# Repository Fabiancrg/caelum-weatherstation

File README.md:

| Supported Targets | ESP32-C6 | ESP32-H2 |
| ----------------- |  -------- | -------- |

# Caelum - Zigbee Weather Station

## Project Description

This project implements a battery-powered environmental monitoring device using ESP32-C6/H2 with Zigbee connectivity. The device features a 3-endpoint design with remote sleep configuration, optimized for low-power operation with deep sleep support and extended wake time during network join.

This project is based on the examples provided in the ESP Zigbee SDK:

* [ESP Zigbee SDK Docs](https://docs.espressif.com/projects/esp-zigbee-sdk)
* [ESP Zigbee SDK Repo](https://github.com/espressif/esp-zigbee-sdk)

## Device Features

### 🌐 Zigbee Endpoints Overview

| Endpoint | Device Type | Clusters | Description |
|----------|-------------|----------|-------------|
| **1** | Environmental Sensor | Temperature, Humidity, Pressure, Battery, OTA | BME280 sensor via I2C |
| **2** | Rain Gauge | Analog Input | Tipping bucket rain sensor with rainfall totals |
| **3** | Sleep Configuration | Analog Input | Remote sleep duration control (60-7200 seconds) |
| **4** | LED Debug Control | On/Off | WS2812 RGB LED status indicator (remote control) |

### 💡 LED Debug Feature (Optional)

The device includes an optional WS2812 RGB LED on GPIO8 (ESP32-H2 SuperMini) that provides visual feedback:
- **Blue (Steady)**: Connected to Zigbee network
- **Orange (Blinking)**: Joining/searching for network  
- **White (Brief Flash)**: Rain pulse detected
- **Off**: Deep sleep or disabled via Zigbee

This feature can be controlled remotely via Zigbee2MQTT (endpoint 4) and disabled to conserve battery. See [LED_DEBUG_FEATURE.md](LED_DEBUG_FEATURE.md) for complete documentation.

### 📋 Detailed Endpoint Descriptions

#### **Endpoint 1: Environmental Monitoring & Power Management**
- **Hardware**: BME280 sensor via I2C
  - **ESP32-H2**: SDA: GPIO10, SCL: GPIO11
  - **ESP32-C6**: SDA: GPIO6, SCL: GPIO7
- **Measurements**: 
  - 🌡️ **Temperature**: -40°C to +85°C (±1°C accuracy)
  - 💧 **Humidity**: 0-100% RH (±3% accuracy) 
  - 🌪️ **Pressure**: 300-1100 hPa (±1 hPa accuracy)
  - 🔋 **Battery Monitoring**: Li-Ion voltage (2.7V-4.2V) and percentage
- **Battery Monitoring**:
  - **Hardware**: GPIO4 (ADC1_CH4) with voltage divider (2x 100kΩ resistors)
  - **Voltage**: Real-time battery voltage in 0.1V units
  - **Percentage**: Battery level 0-100% based on Li-Ion discharge curve
  - **Calibration**: ESP32-H2 ADC correction factor (1.604x) for accurate readings
  - **Power Configuration Cluster**: Standard Zigbee battery attributes
  - **Optimized Reading**: 
    - Time-based hourly intervals (3600 seconds) with NVS persistence
    - 3 ADC samples (reduced from 10) for ~70% ADC power savings
    - No delays between samples for ~90% overhead reduction
    - Total battery monitoring power: ~12µAh/day (98% reduction from ~480µAh/day)
    - Always reports on first boot/pairing, then hourly regardless of wake frequency
- **Features**: Automatic reporting during wake cycles, Zigbee-standard units
- **Use Case**: Weather monitoring, HVAC automation, air quality tracking, battery-powered applications

#### **Endpoint 2: Rain Gauge System**
- **Hardware**: Tipping bucket rain gauge with reed switch
  - **ESP32-H2**: GPIO12 (RTC-capable for sleep wake-up)
  - **ESP32-C6**: GPIO5 (RTC-capable for sleep wake-up)
- **Measurements**: Cumulative rainfall in millimeters (0.36mm per tip)
- **Features**: 
  - Advanced debouncing (200ms + 1000ms bounce settle)
  - Persistent storage (NVS) for total tracking
  - Smart reporting (1mm threshold OR hourly)
  - Network-aware operation (only active when connected)
  - **Both targets**: Wake from deep sleep on rain detection
  - **Time-based hourly reading**: Uses NVS persistence to ensure true 1-hour intervals regardless of wake frequency
- **Specifications**: 
  - Maximum rate: 200mm/hour supported
  - Accuracy: ±0.36mm per bucket tip
  - Storage: Non-volatile total persistence across reboots
  - Rain-proof interval tracking: Hourly battery reading even during frequent rain events
- **Use Case**: Weather station, irrigation control, flood monitoring

#### **Endpoint 3: Sleep Configuration**
- **Hardware**: Software-only (virtual endpoint)
- **Control**: Sleep duration in seconds (60-7200s range)
- **Features**:
  - Remote configuration via Zigbee2MQTT or Home Assistant
  - Persistent storage (NVS) - survives reboots
  - Real-time updates - changes apply on next wake cycle
  - Default: 900 seconds (15 minutes)
- **Use Case**: 
  - Battery optimization (longer intervals = longer battery life)
  - Seasonal adjustments (frequent updates in rainy season)
  - Dynamic power management based on weather conditions

#### **Endpoint 4: LED Debug Control**
- **Hardware**: WS2812 RGB LED (ESP32-H2 SuperMini)
  - **GPIO**: GPIO8
  - **Driver**: espressif/led_strip ~2.0.0
- **LED States**:
  - 🔵 **Blue (Steady)**: Connected to Zigbee network
  - 🟠 **Orange (Blinking)**: Searching/joining network
  - ⚪ **White (Flash)**: Rain pulse detected (100ms)
  - ⚫ **Off**: Deep sleep or disabled
- **Control**: On/Off cluster for remote enable/disable
- **Features**:
  - Remote control via Zigbee2MQTT switch
  - Default state: Enabled (ON)
  - Minimal battery impact (~20mA when active, off during sleep)
  - Visual feedback for debugging and network status
- **Use Case**: 
  - Development and testing (visual network status)
  - Field deployment debugging
  - Can be disabled remotely to conserve battery
- **Documentation**: See [LED_DEBUG_FEATURE.md](LED_DEBUG_FEATURE.md) for details

### 🔧 Hardware Configuration

#### **Required Components**
- ESP32-C6 or ESP32-H2 development board
- BME280 environmental sensor module
- Tipping bucket rain gauge with reed switch
- Li-Ion battery (with protection circuit, 5V output recommended)
- Voltage divider (2x 100kΩ resistors for battery monitoring)
- Zigbee coordinator (ESP32-H2 or commercial gateway)

#### **Pin Assignments**

**ESP32-H2 (Recommended)**
```
GPIO 4  - Battery voltage input (ADC1_CH4 with voltage divider)
GPIO 8  - WS2812 RGB LED (debug indicator, optional)
GPIO 9  - Built-in button (factory reset)
GPIO 10 - I2C SDA (BME280)
GPIO 11 - I2C SCL (BME280) 
GPIO 12 - Rain gauge input (RTC-capable)*
```

**ESP32-C6**
```
GPIO 4  - Battery voltage input (ADC1_CH4 with voltage divider)
GPIO 5  - Rain gauge input (RTC-capable)*
GPIO 6  - I2C SDA (BME280)
GPIO 7  - I2C SCL (BME280) 
GPIO 9  - Built-in button (factory reset)
```

*Both targets now use RTC-capable GPIO pins for rain detection during deep sleep

**Battery Voltage Divider Circuit**
```
Battery+ ──┬── 100kΩ ──┬── 100kΩ ── GND
           │           │
           │           └── GPIO4 (ADC input)
           │
           └── 5V output (to ESP32 power)
```
Note: Voltage divider monitors the cell voltage (2.7V-4.2V) while the battery pack provides 5V regulated output

### � Zigbee Integration
- **Protocol**: Zigbee 3.0  
- **Device Type**: End Device (sleepy end device for battery operation)
- **Supported Channels**: 11-26 (2.4 GHz)
- **Compatible**: Zigbee2MQTT, Home Assistant ZHA, Hubitat
- **OTA Support**: Over-the-air firmware updates enabled (see [OTA_GUIDE.md](OTA_GUIDE.md))

### ⚡ Power Management
- **Deep Sleep Mode**: Configurable intervals (60-7200 seconds, default 15 minutes)
  - **Configurable via Zigbee2MQTT**: Adjust sleep duration remotely from Home Assistant
  - **Connected**: Uses configured interval (default 15 minutes)
  - **Disconnected**: 30-second intervals for quick reconnection
  - **Max retries**: After 20 attempts (10 minutes), reduces to half configured duration
  - **Extended wake time**: Device stays awake for 60 seconds when not connected (instead of 10s) to allow Zigbee join process to complete
- **Wake-up Sources**:
  - Timer (configurable 60-7200 seconds)
  - **Rain detection during deep sleep** (both targets support RTC wake-up)
    - **ESP32-H2**: GPIO12 (RTC-capable)
    - **ESP32-C6**: GPIO5 (RTC-capable)
- **Network Retry Logic**: 
  - Prevents deep sleep when not connected to ensure reliable pairing
  - Extended 60-second wake period for join process completion
  - Connection success triggers 15-second reporting window before sleep
- **Battery Life**: Optimized for extended operation on battery power
  - **Total Power Consumption**: ~230µAh/day (optimized from ~700µAh/day)
  - **Battery monitoring**: ~12µAh/day (hourly readings with time-based intervals)
  - **Deep sleep**: 7-10µA baseline
  - **Active time**: ~100mA during 15-minute wake cycles
- **Battery Estimate**: 
  - **2500mAh battery**: ~10.9 years (optimized from ~3.5 years)
  - **Optimization breakdown**: 
    - 3 ADC samples instead of 10 (70% ADC power savings)
    - No delays between samples (90% overhead reduction)
    - Time-based hourly intervals (vs. every wake cycle)
    - Total battery monitoring: 98% power reduction

## 🚀 Quick Start

### Prerequisites

```bash
# Install ESP-IDF v5.5.1 or later
git clone -b v5.5.1 --recursive https://github.com/espressif/esp-idf.git
cd esp-idf
# For ESP32-H2 (recommended)
./install.sh esp32h2
# For ESP32-C6
./install.sh esp32c6
. ./export.sh
```

### Configure the Project
```bash
# For ESP32-H2 (recommended for better power management)
idf.py set-target esp32h2
# For ESP32-C6  
idf.py set-target esp32c6
idf.py menuconfig
```

### Build and Flash
```bash
# Erase previous data (recommended for first flash)
idf.py -p [PORT] erase-flash

# Build and flash the project
idf.py -p [PORT] flash monitor
```

### 🛠️ Configuration

### Device Operation

#### **Factory Reset**
- **Built-in Button (GPIO 9)**:
  - Long press (5s): Factory reset device

#### **Automatic Features**
- Environmental data reported during wake cycles
- Rain gauge totals stored persistently in NVS
- Smart rainfall reporting (1mm increments or hourly)
- Network connection status monitoring
- Deep sleep after data reporting (15-second window when connected, 60 seconds when not connected)
- Sleep duration remotely configurable via Zigbee2MQTT (60-7200 seconds)

### 📡 Data Reporting
- **Temperature/Humidity/Pressure**: Reported during wake cycles
- **Rainfall**: Immediate on tip detection (>1mm) or hourly
- **Sleep Duration**: Configurable 60-7200 seconds (default 15 minutes)
- **Sleep Cycle**: Configurable via Endpoint 3 for battery optimization

## 📊 Example Output

### Device Initialization
```
I (403) app_start: Starting scheduler on CPU0
I (408) WEATHER_STATION: Initialize Zigbee stack
I (558) WEATHER_STATION: Deferred driver initialization successful
I (568) WEATHER_STATION: BME280 sensor initialized successfully
I (578) WEATHER_STATION: Rain gauge initialized. Current total: 0.00 mm
I (578) WEATHER_STATION: Start network steering
```

### Network Connection
```
I (3558) WEATHER_STATION: Joined network successfully (Extended PAN ID: 74:4d:bd:ff:fe:63:f7:30, PAN ID: 0x13af, Channel:13, Short Address: 0x7c16)
I (3568) RAIN_GAUGE: Rain gauge enabled - device connected to Zigbee network
```

### Sensor Data Reporting
```
I (8000) WEATHER_STATION: 🌡️ Temperature: 22.35°C reported to Zigbee  
I (8010) WEATHER_STATION: 💧 Humidity: 45.20% reported to Zigbee
I (8020) WEATHER_STATION: 🌪️ Pressure: 1013.25 hPa reported to Zigbee
I (8030) BATTERY: 🔋 Li-Ion Battery: 4.17V (98%) - Zigbee values: 41 (0.1V), 196 (%*2)
I (8040) WEATHER_STATION: 📡 Temp: 22.4°C
I (8050) WEATHER_STATION: 📡 Humidity: 45.2%
I (8060) WEATHER_STATION: 📡 Pressure: 1013.3 hPa
```

### Rain Gauge Activity
```  
I (10000) RAIN_GAUGE: 🔍 Rain gauge interrupt received on GPIO18 (enabled: YES)
I (10010) RAIN_GAUGE: 🌧️ Rain pulse #1 detected! Total: 0.36 mm (+0.36 mm)
I (10020) RAIN_GAUGE: ✅ Rainfall total 0.36 mm reported to Zigbee
I (10030) WEATHER_STATION: 📡 Rain: 0.36 mm
```

### Deep Sleep Entry
```
I (18000) WEATHER_STATION: ⏳ Preparing for deep sleep...
I (18010) WEATHER_STATION: 💤 Entering deep sleep for 900 seconds (15 minutes)
```

## 🏠 Home Assistant Integration

When connected to Zigbee2MQTT or other Zigbee coordinators, the device appears as:

- **4x Sensor entities**: Temperature, Humidity, Pressure, Battery Percentage
- **1x Sensor entity**: Battery Voltage (mV)
- **1x Sensor entity**: Rainfall total with automatic updates
- **1x Number entity**: Sleep duration control (60-7200 seconds)
- **1x Switch entity**: LED debug control (enable/disable status indicator)

### Zigbee2MQTT Integration

A custom external converter is provided for full feature support with Zigbee2MQTT. See [ZIGBEE2MQTT_CONVERTER.md](ZIGBEE2MQTT_CONVERTER.md) for:
- Converter installation instructions
- Multi-endpoint support configuration
- Sleep duration control setup
- Home Assistant automation examples

### Device Information
- **Manufacturer**: ESPRESSIF
- **Model**: caelum
- **Firmware Version**: Managed via CMakeLists.txt (PROJECT_VER, BUILD_NUMBER)
  - Generated header approach using `version.h.in` template
  - Single source of truth for all version macros
  - Automatically propagated to Zigbee Basic cluster attributes
- **Supported**: Zigbee2MQTT with custom external converter (`caelum-weather-station.js`)

## 🔧 Configuration

### Version Management

Version information is centrally managed in `CMakeLists.txt`:

```cmake
set(PROJECT_VER "1.0")           # Major.Minor version
set(BUILD_NUMBER 0)              # Build/patch number
```

The build system automatically:
- Generates `build/generated/version.h` from `version.h.in` template
- Populates all version macros (FW_VERSION, FW_DATE_CODE, OTA_FILE_VERSION, etc.)
- Propagates to Zigbee Basic cluster (swBuildId, dateCode, applicationVersion)
- Updates OTA cluster attributes for firmware update tracking

### Application Configuration

Key parameters can be adjusted in `main/esp_zb_weather.h`:
- Default sleep duration: 900 seconds (15 minutes) - can be changed via Endpoint 3
- Sleep duration range: 60-7200 seconds (1 minute to 2 hours)
- Network retry interval: 30 seconds when disconnected
- Maximum connection retries: 20 attempts before reducing sleep interval
- Rain tip bucket volume: 0.36mm per tip
- Extended wake time: 60 seconds when not connected (for join process)
- **Battery monitoring interval**: 3600 seconds (1 hour) - time-based with NVS persistence
- **Battery ADC samples**: 3 samples averaged (optimized from 10)
- **Battery monitoring power**: ~12µAh/day (98% reduction from original ~480µAh/day)
- **LED Debug**: Optional WS2812 RGB LED on GPIO8 (ESP32-H2), controllable via Zigbee

## 📝 Project Structure

```
WeatherStation/
├── main/
│   ├── esp_zb_weather.c     # Main Zigbee stack, 4-endpoint logic, network retry, LED control
│   ├── esp_zb_weather.h     # Configuration, endpoint definitions, LED settings
│   ├── esp_zb_ota.c         # OTA update implementation
│   ├── esp_zb_ota.h         # OTA interface
│   ├── sleep_manager.c      # Deep sleep management with RTC GPIO support
│   ├── sleep_manager.h      # Sleep manager interface
│   ├── bme280_app.c         # BME280 sensor driver with board-specific I2C
│   ├── bme280_app.h         # BME280 interface
│   ├── weather_driver.c     # DEPRECATED: Legacy driver (unused)
│   └── weather_driver.h     # DEPRECATED: Legacy interface (unused)
├── Doc/
│   └── README_GIT.md        # Git workflow guide for team (Azure DevOps)
├── caelum-weather-station.js # Zigbee2MQTT external converter (4 endpoints)
├── version.h.in             # Version header template (for configure_file)
├── CMakeLists.txt           # Build configuration with version generation
├── partitions.csv           # Partition table with OTA support
├── sdkconfig.defaults       # Default SDK settings
├── OTA_GUIDE.md            # OTA update instructions
├── LED_DEBUG_FEATURE.md    # LED debug feature documentation
└── README.md               # This file
```

## 🔧 Troubleshooting

### Common Issues

#### **Rain Gauge Not Detecting**
- **ESP32-H2**: Verify GPIO12 connections and reed switch operation
- **ESP32-C6**: Verify GPIO5 connections and reed switch operation
- Check that device is connected to Zigbee network (rain gauge only active when connected)
- Ensure proper pull-down resistor on rain gauge input
- Both targets support rain detection during deep sleep

#### **BME280 Not Reading**  
- **ESP32-H2**: Check I2C connections (SDA: GPIO10, SCL: GPIO11)
- **ESP32-C6**: Check I2C connections (SDA: GPIO6, SCL: GPIO7)
- Verify BME280 I2C address (default: 0x76 or 0x77)
- Ensure proper power supply to sensor (3.3V)

#### **Battery Monitoring Issues**
- Verify voltage divider connections (2x 100kΩ resistors to GPIO4)
- Check battery cell voltage tap (should be 2.7V-4.2V at divider output)
- Ensure GPIO4 (ADC1_CH4) is properly configured
- Monitor serial output for ADC calibration messages
- **ESP32-H2 ADC quirk**: Uses empirical correction factor (1.604x) for DB_12 attenuation
- Battery percentage calculated from voltage (2.7V=0%, 4.2V=100%)
- **Optimized reading schedule**: 
  - First reading always happens on boot/pairing
  - Subsequent readings every hour (3600 seconds) based on elapsed time
  - Uses NVS to persist timestamp across deep sleep cycles
  - Robust to frequent wake-ups (e.g., during rain events)

#### **Zigbee Connection Issues**
- Perform factory reset with long press (5s) on built-in button
- Ensure Zigbee coordinator is in pairing mode
- Check channel compatibility between coordinator and device
- **Auto-retry**: Device automatically retries every 30 seconds when disconnected
- **Extended wake time**: Device now stays awake for 60 seconds (instead of 10s) during join attempts
- **Battery impact**: Extended connection attempts may drain battery faster
- **Join timing**: Allow full 60 seconds for device to complete Zigbee join process

#### **Device Not Waking from Sleep**
- Check battery voltage (minimum 3.0V recommended)
- Verify wake-up sources (timer, rain gauge)
- Review sleep manager logs for errors
- **Network dependency**: Device stays awake longer when not connected to network

#### **High Battery Drain**
- Check if device is stuck in connection retry mode (30-second intervals)
- Verify Zigbee network is stable and accessible
- Monitor connection retry count in device logs
- Consider factory reset if connection issues persist
- **Battery monitoring optimization**: Should consume only ~12µAh/day (hourly readings)
- **Total optimized power**: ~230µAh/day → 10.9 year battery life (2500mAh battery)
- **LED Debug**: If enabled, LED consumes ~20mA during wake cycles (can be disabled via Zigbee)

#### **LED Not Working**
- **ESP32-H2 SuperMini**: Verify GPIO8 connection to WS2812 RGB LED
- Check LED debug feature is enabled in `esp_zb_weather.h` (`DEBUG_LED_ENABLE=1`)
- Verify LED debug is enabled via Zigbee2MQTT switch (endpoint 4)
- Monitor serial output for LED initialization messages
- Ensure led_strip component (~2.0.0) is properly installed
- **LED States**: Blue=connected, Orange blink=joining, White flash=rain, Off=sleep/disabled
- See [LED_DEBUG_FEATURE.md](LED_DEBUG_FEATURE.md) for detailed troubleshooting

### 📋 Development Notes

- **ESP-IDF Version**: v5.5.1 recommended
- **Zigbee SDK**: Latest ESP Zigbee SDK required  
- **Memory Usage**: ~2MB flash, ~200KB RAM typical
- **Power Consumption**: 
  - Active: ~100mA
  - Deep sleep: 7-10µA
  - Battery monitoring: ~12µAh/day (optimized)
  - **Total**: ~230µAh/day (3.1× improvement from ~700µAh/day)
- **Battery Operation**: Optimized for CR123A or Li-ion battery packs
  - **2500mAh battery**: ~10.9 years (vs. 3.5 years before optimization)
- **Target Support**: Both ESP32-H2 and ESP32-C6 fully support RTC GPIO wake-up for rain detection
- **Version Management**: Centralized in CMakeLists.txt with generated header approach

## 🔄 OTA Updates

This project supports Over-The-Air (OTA) firmware updates via Zigbee network. See [OTA_GUIDE.md](OTA_GUIDE.md) for detailed instructions on:
- Creating OTA images
- Configuring Zigbee2MQTT for OTA
- Performing updates
- Troubleshooting OTA issues

## 📄 License

This project follows dual licensing:
- **Software**: GNU General Public License v3.0 (see [LICENSE](LICENSE))
- **Hardware**: Creative Commons Attribution-NonCommercial-ShareAlike 4.0 (see [LICENSE-hardware](LICENSE-hardware))

## 🔄 Based On

This project is derived from ESP32 Zigbee SDK examples and implements a 4-endpoint architecture optimized for battery-powered weather station applications with:
- Remote sleep duration configuration (Endpoint 3)
- LED debug status indicator with remote control (Endpoint 4)
- Deep sleep power management with network retry logic
- Extended wake time during Zigbee join process (60 seconds)
- RTC GPIO wake-up support for rain detection on both ESP32-H2 and ESP32-C6
- Optimized battery monitoring with 98% power reduction

## 🤝 Contributing

Contributions are welcome! Please feel free to submit issues or pull requests.

For technical queries, please open an issue on GitHub. Include:
- Complete serial monitor output
- Hardware configuration details  
- ESP-IDF and SDK versions
- Specific symptoms and reproduction steps

## 💖 Support

If you find this project useful, consider supporting the development:

---

**Project**: Caelum - ESP32 Zigbee Weather Station  
**Version**: Managed via CMakeLists.txt (PROJECT_VER, BUILD_NUMBER)  
**Compatible**: ESP32-C6, ESP32-H2, ESP-IDF v5.5.1+  
**License**: GPL v3 (Software) / CC BY-NC-SA 4.0 (Hardware)  
**Features**: 
- 4-endpoint design (sensors, rain, sleep config, LED debug)
- Remote sleep configuration and LED control via Zigbee
- OTA firmware updates
- RTC GPIO wake-up for rain detection
- Optimized battery monitoring (~98% power reduction)
- Time-based hourly intervals with NVS persistence
- WS2812 RGB LED status indicator (optional)
- 10.9 year battery life (2500mAh, 15-min intervals)

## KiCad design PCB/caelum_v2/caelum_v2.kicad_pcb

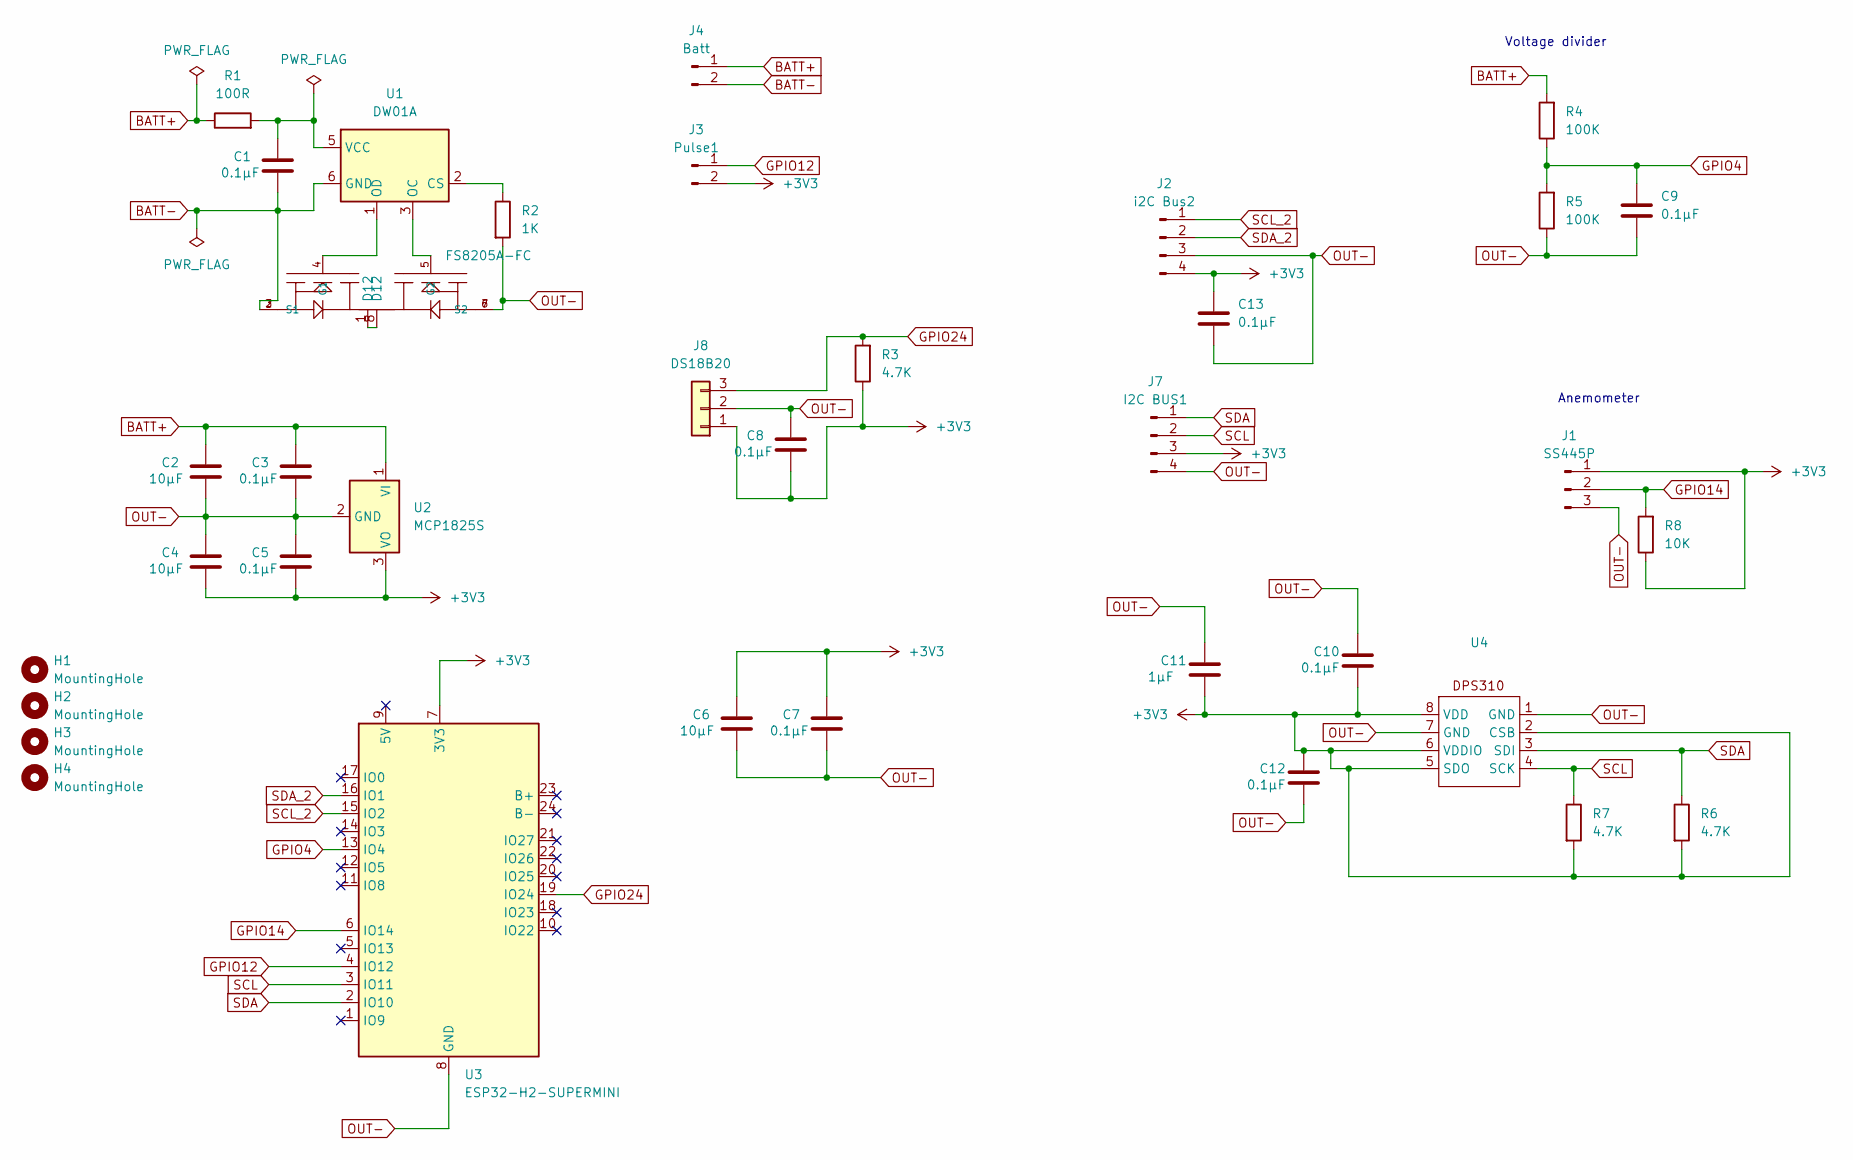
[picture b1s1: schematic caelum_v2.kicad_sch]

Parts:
C1, C3, C5, C7, C8, C9, C10, C12, C13: 0.1µF; C_0805_2012Metric
C2, C4, C6: 10µF; C_0805_2012Metric
C11: 1µF; C_0805_2012Metric
H1, H2, H3, H4: MountingHole; MountingHole_2.2mm_M2
J1: SS445P; Hirose_DF13C_CL535-0403-5-51_1x03-1MP_P1.25mm_Vertical
J2: i2C Bus2; JST_PH_B4B-PH-SM4-TB_1x04-1MP_P2.00mm_Vertical
J3: Pulse1; Hirose_DF13C_CL535-0402-2-51_1x02-1MP_P1.25mm_Vertical
J4: Batt; PinHeader_1x02_P2.54mm_Vertical
J7: I2C BUS1; JST_PH_S4B-PH-SM4-TB_1x04-1MP_P2.00mm_Horizontal
J8: DS18B20; Hirose_DF13C_CL535-0403-5-51_1x03-1MP_P1.25mm_Vertical
Q1: FS8205A-FC; SOP65P640X120-8N-FC; PARTREV 1.7
R1: 100R; R_0805_2012Metric
R2: 1K; R_0805_2012Metric
R3, R6, R7: 4.7K; R_0805_2012Metric
R4, R5: 100K; R_0805_2012Metric
R8: 10K; R_0805_2012Metric
U1: DW01A; SOT-23-6
U2: MCP1825S; SOT-223-3_TabPin2
U3: ESP32-H2-SUPERMINI; ESP32H2-Supermini
U4: Bosch_LGA-8_2x2.5mm_P0.65mm_ClockwisePinNumbering

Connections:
+3V3: C4.2, C5.2, C6.1, C7.1, C8.2, C10.2, C11.2, C12.1, C13.1, J1.1, J2.4, J3.2, J7.3, J8.1, R3.1, R6.2, R7.2, R8.1, U2.3 (VO), U3.7 (3V3), U4.2 (CSB), U4.5 (SDO), U4.6 (VDDIO), U4.8 (VDD)
BATT+: C2.1, C3.1, J4.1, R1.1, R4.2, U2.1 (VI)
BATT-: C1.2, J4.2, Q1.2 (S1), Q1.3 (S1), U1.6 (GND)
GPIO4: C9.1, R4.1, R5.2, U3.13 (IO4)
GPIO12: J3.1, U3.4 (IO12)
GPIO14: J1.2, R8.2, U3.6 (IO14)
GPIO24: J8.3, R3.2, U3.19 (IO24)
unnamed: Q1.1 (D12), Q1.8 (D12)
unnamed: Q1.4 (G1), U1.1 (OD)
unnamed: Q1.5 (G2), U1.3 (OC)
unnamed: R2.1, U1.2 (CS)
unnamed: C1.1, R1.2, U1.5 (VCC)
OUT-: C2.2, C3.2, C4.1, C5.1, C6.2, C7.2, C8.1, C9.2, C10.1, C11.1, C12.2, C13.2, J1.3, J2.3, J7.4, J8.2, Q1.6 (S2), Q1.7 (S2), R2.2, R5.1, U2.2 (GND), U3.8 (GND), U4.1 (GND), U4.7 (GND)
SCL: J7.2, R7.1, U3.3 (IO11), U4.4 (SCK)
SCL_2: J2.1, U3.15 (IO2)
SDA: J7.1, R6.1, U3.2 (IO10), U4.3 (SDI)
SDA_2: J2.2, U3.16 (IO1)

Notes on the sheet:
Anemometer
Voltage divider

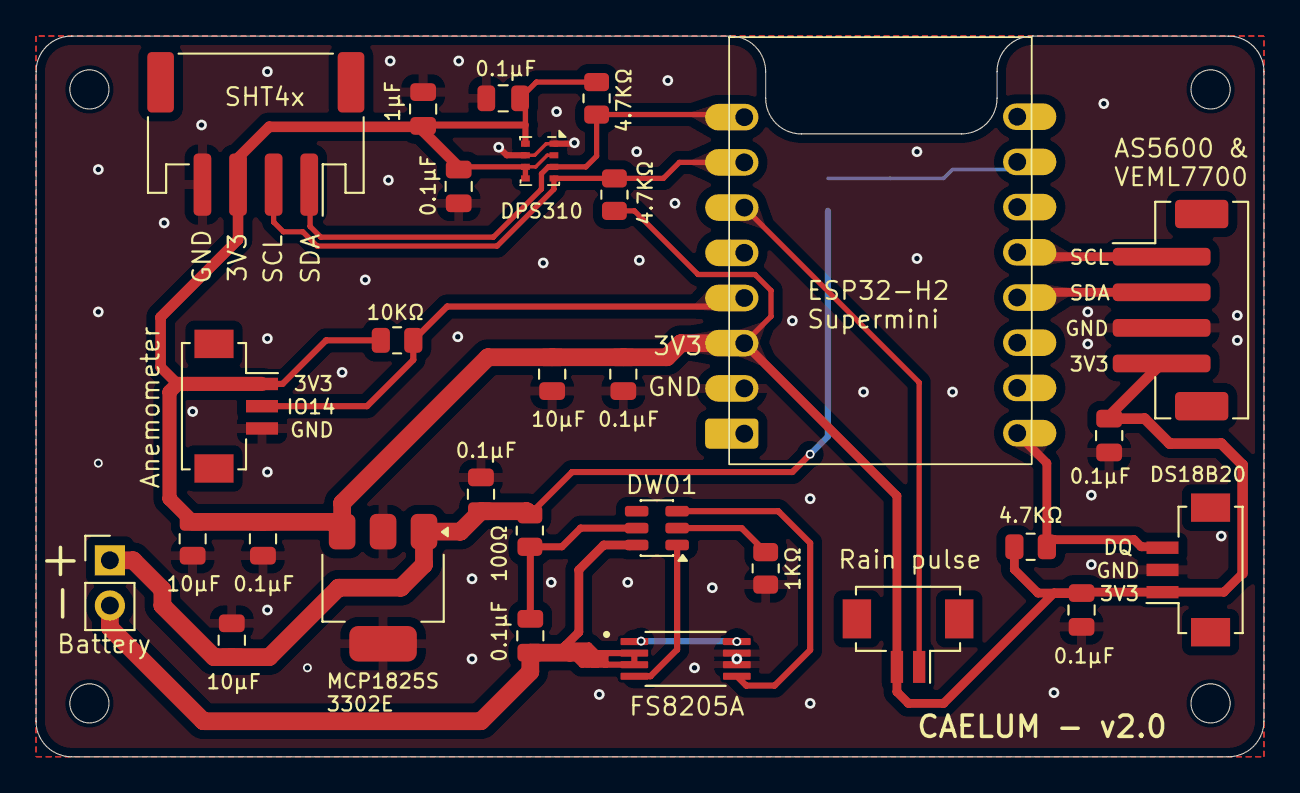
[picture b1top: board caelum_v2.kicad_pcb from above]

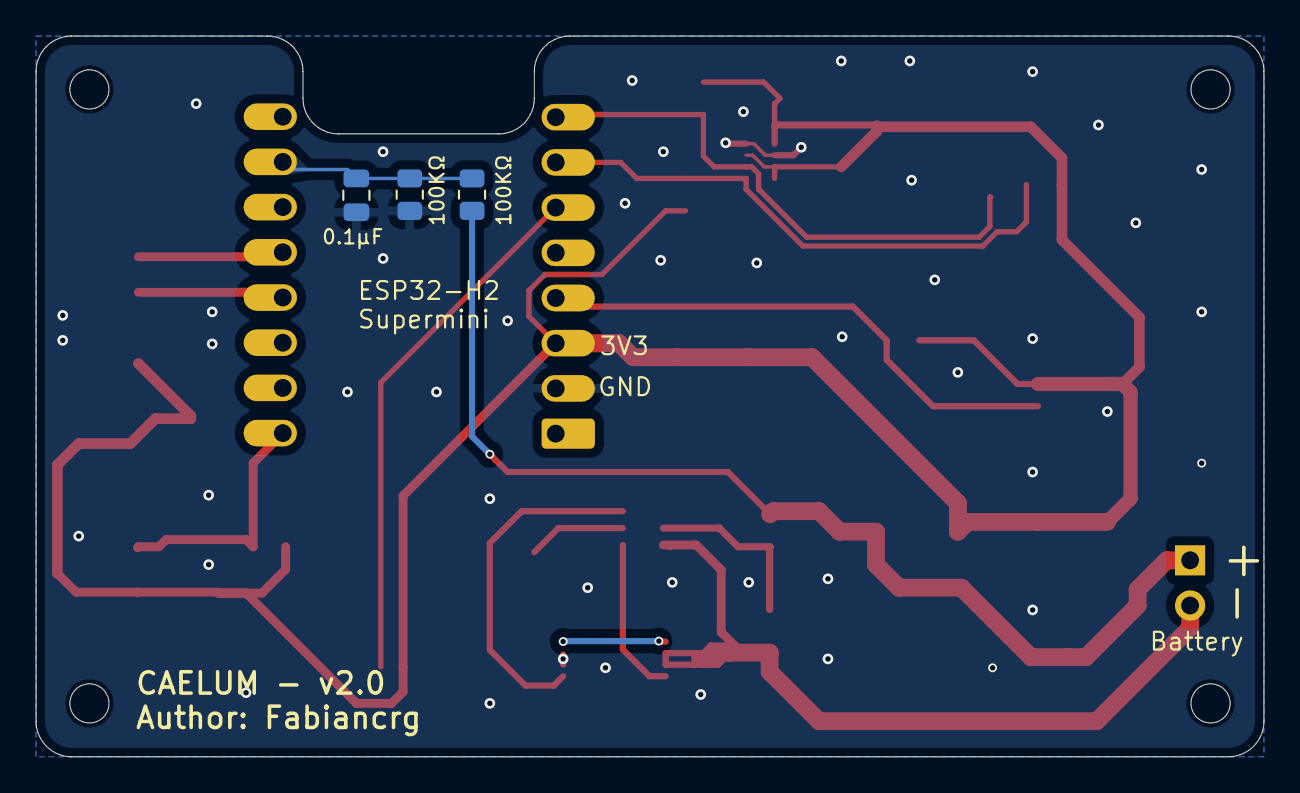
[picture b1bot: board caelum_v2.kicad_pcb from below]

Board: 2 copper layers, 69.0 x 40.5 mm, 36 parts (3 on the bottom side), 17 nets.

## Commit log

2025-10-16 Add LICENSE file with GPL v3.0 terms
2025-10-16 Add hardware license under CC BY-NC-SA 4.0
    Added a hardware license file outlining the terms for hardware design files.
2025-11-05 Implement OTA functionality for Zigbee updates and add OTA guide documentation
2025-11-05 Refactor project structure and enhance functionality: update CMakeLists.txt, README, and add sleep management features; integrate Zigbee OTA support and create external converter for Zigbee2MQTT.
2025-11-05 Update README and esp_zb_weather.c to enhance rain gauge functionality and sleep management
    - Revised project description and added details for the new 3-endpoint design in README.md.
    - Implemented deferred driver initialization and improved logging in esp_zb_weather.c.
    - Removed unused NVS functions for rain gauge data storage, now handled by sleep manager.
    - Enhanced rain gauge task with better ISR handling and periodic debug logging.
    - Scheduled final sensor reporting before deep sleep and ensured Zigbee stack suspension.
2025-11-06 Enhance weather station functionality: update description, add rainfall and sleep duration metrics, implement OTA status checks, and ensure deep sleep scheduling respects OTA updates.
2025-11-06 Add battery monitoring functionality and update ADC configuration
2025-11-06 Refactor converter for battery monitoring: remove manual handling of battery data and streamline integration with existing functionality
2025-11-06 Update project version to 0.2 and change module export syntax in weather station code
2025-11-06 Add debug LED functionality for network status indication
2025-11-08 Comment out unused variable last_debug_time in rain_gauge_task for clarity
2025-11-08 Update build number to 20 and adjust sensor reporting delays for improved performance
2025-11-09 Migrate from deep sleep to light sleep mode for ESP32-H2 Weather Station, enhancing responsiveness and maintaining Zigbee connection. Update related functions and documentation.
2025-11-10 Update build number to 30 for version 1.3 (Test OTA)
2025-11-11 Enable power management features and adjust logging levels in sdkconfig
2025-11-12 Refactor initial sensor data reporting and LED deinitialization logic for improved battery efficiency. Update reporting configuration to ensure persistence across reboots and enhance logging for attr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
2025-11-12 Remove optional sleep cycle logging to reduce power consumption during sleep. Ensure LED deinitialization is handled after successful join.
2025-11-15 Update partitions.csv for ESP32-H2 with 4MB Flash configuration
    - Adjusted partition sizes and offsets to optimize for OTA updates.
    - Reduced NVS size to 0x4000 and updated offsets for phy_init and otadata.
    - Modified OTA partition sizes to fit within the new 4MB flash limit.
    - Ensured compatibility with the new memory layout for better performance.
2025-12-03 Add Pulse counter on GPIO13
2025-12-08 feat: Configure local reporting for rain gauge and pulse counter endpoints
2025-12-14 Add PCB v2
2025-12-15 Update PCB V2
2025-12-26 Fix BMP280 + SHT41 combo : Read of P is fixed
2025-12-26 Fix: OTA issue with sleep device
2025-12-27 Update build number to 10 and enhance OTA logging for better debugging
2025-12-27 Enhance OTA handling: Prevent sensor readings during OTA transfer to avoid timeouts
2025-12-27 Update build number to 30 for versioning consistency
2025-12-28 Add dedicated sensor reading task to prevent blocking Zigbee scheduler

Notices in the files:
README.md:
License: CC BY-NC-SA 4.0
